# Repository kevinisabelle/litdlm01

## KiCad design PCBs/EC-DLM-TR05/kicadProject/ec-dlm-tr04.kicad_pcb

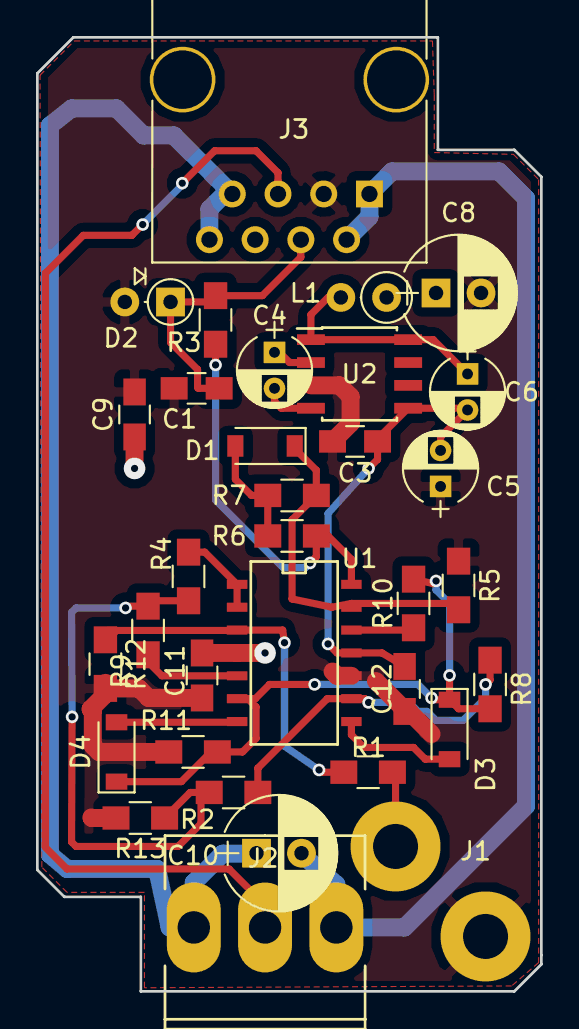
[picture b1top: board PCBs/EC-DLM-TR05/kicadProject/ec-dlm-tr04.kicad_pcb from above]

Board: 2 copper layers, 28.0 x 53.0 mm, 33 parts (0 on the bottom side), 23 nets.

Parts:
C1, C3, C9, C11, C12: 100n; C_0805_HandSoldering
C4, C5: 10u; CP_Radial_D4.0mm_P2.00mm
C6: 100u; CP_Radial_D4.0mm_P2.00mm
C8: 10u; CP_Radial_D6.3mm_P2.50mm
C10: 10uf; CP_Radial_D6.3mm_P2.50mm
D1: 1N4148; D_SOD-123
D2: 1N4148; D_DO-35_SOD27_P2.54mm_Vertical_AnodeUp
D3, D4: D; D_SOD-123
J1: input; WireConnection_2.50mmDrill
J2: LED Connector; Socket_MOLEX-KK-RM3-96mm_Lock_3pin_straight
J3: RJ45; RJ45_8
L1: Ferrite_Bead; L_Axial_L6.6mm_D2.7mm_P2.54mm_Vertical_Vishay_IM-2
R1, R7: 100k; R_0805_HandSoldering
R2, R3, R4, R5, R6, R8, R9, R10, R11: 10k; R_0805_HandSoldering
R12, R13: 1M; R_0805_HandSoldering
U1: TL074; SOIC-14_N
U2: TC1044S; SOIC-8_3.9x4.9mm_Pitch1.27mm

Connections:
ADCTrig: C1.2, D2.1, J3.4, R3.2
AGND: C1.1, C3.2, C5.1, C8.2, C9.1, C11.2, C12.2, D2.2, J1.1, J3.3, R5.2, R11.1, R12.2, R13.2, U1.10, U2.3
AVCC: C8.1, C9.2, C11.1, J3.6, L1.1, U1.4
AVSS: C3.1, C5.2, C6.2, C12.1, U1.11, U2.5
GND: C10.2, J2.1, J3.1, J3.2
L_OUT_5: J2.2, J3.5
unnamed: C4.1, U2.2
unnamed: C4.2, U2.4
unnamed: C6.1, L1.2, U2.1, U2.8
unnamed: D1.1, R5.1, R7.2, U1.13
unnamed: D1.2, R6.1, R7.1
unnamed: D3.1, D4.1, R8.1, R10.2, R11.2, U1.6
unnamed: D3.2, U1.8
unnamed: D4.2, U1.7
unnamed: J1.2, R1.2
unnamed: R1.1, R12.1, U1.3
unnamed: R2.1, R8.2, U1.9
unnamed: R3.1, R6.2, U1.14
unnamed: R4.2, U1.1, U1.2
unnamed: R9.2, U1.5
unnamed: R10.1, U1.12
unnamed: R2.2, R4.1, R9.1, R13.1
VCC5: C10.1, J2.3, J3.7, J3.8

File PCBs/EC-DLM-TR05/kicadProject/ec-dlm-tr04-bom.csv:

Reference, Value, Footprint, Datasheet
"J3","RJ45","Connectors:RJ45_8",""
"J2","LED Connector","Sockets_MOLEX_KK-System:Socket_MOLEX-KK-RM3-96mm_Lock_3pin_straight",""
"U1","TL074","SMD_Packages:SOIC-14_N",""
"R1","100k","Resistors_SMD:R_0805_HandSoldering",""
"J1","input","Wire_Connections_Bridges:WireConnection_2.50mmDrill",""
"R2","10k","Resistors_SMD:R_0805_HandSoldering",""
"R4","10k","Resistors_SMD:R_0805_HandSoldering",""
"R5","10k","Resistors_SMD:R_0805_HandSoldering",""
"R6","10k","Resistors_SMD:R_0805_HandSoldering",""
"D1","1N4148","Diodes_SMD:D_SOD-123",""
"D2","1N4148","Diodes_THT:D_DO-35_SOD27_P2.54mm_Vertical_AnodeUp",""
"R3","10k","Resistors_SMD:R_0805_HandSoldering",""
"C1","100n","Capacitors_SMD:C_0805_HandSoldering",""
"U2","TC1044S","Housings_SOIC:SOIC-8_3.9x4.9mm_Pitch1.27mm",""
"C4","10u","Capacitors_THT:CP_Radial_D4.0mm_P2.00mm",""
"C5","10u","Capacitors_THT:CP_Radial_D4.0mm_P2.00mm",""
"C6","100u","Capacitors_THT:CP_Radial_D4.0mm_P2.00mm",""
"L1","Ferrite_Bead","Inductors_THT:L_Axial_L6.6mm_D2.7mm_P2.54mm_Vertical_Vishay_IM-2",""
"R13","1M","Resistors_SMD:R_0805_HandSoldering",""
"R8","10k","Resistors_SMD:R_0805_HandSoldering",""
"D4","D","Diodes_SMD:D_SOD-123",""
"D3","D","Diodes_SMD:D_SOD-123",""
"R9","10k","Resistors_SMD:R_0805_HandSoldering",""
"R10","10k","Resistors_SMD:R_0805_HandSoldering",""
"R11","10k","Resistors_SMD:R_0805_HandSoldering",""
"R12","1M","Resistors_SMD:R_0805_HandSoldering",""
"R7","100k","Resistors_SMD:R_0805_HandSoldering",""
"C9","100n","Capacitors_SMD:C_0805_HandSoldering",""
"C10","10uf","Capacitors_THT:CP_Radial_D6.3mm_P2.50mm",""
"C3","100n","Capacitors_SMD:C_0805_HandSoldering",""
"C8","10u","Capacitors_THT:CP_Radial_D6.3mm_P2.50mm",""
"C11","100n","Capacitors_SMD:C_0805_HandSoldering",""
"C12","100n","Capacitors_SMD:C_0805_HandSoldering",""

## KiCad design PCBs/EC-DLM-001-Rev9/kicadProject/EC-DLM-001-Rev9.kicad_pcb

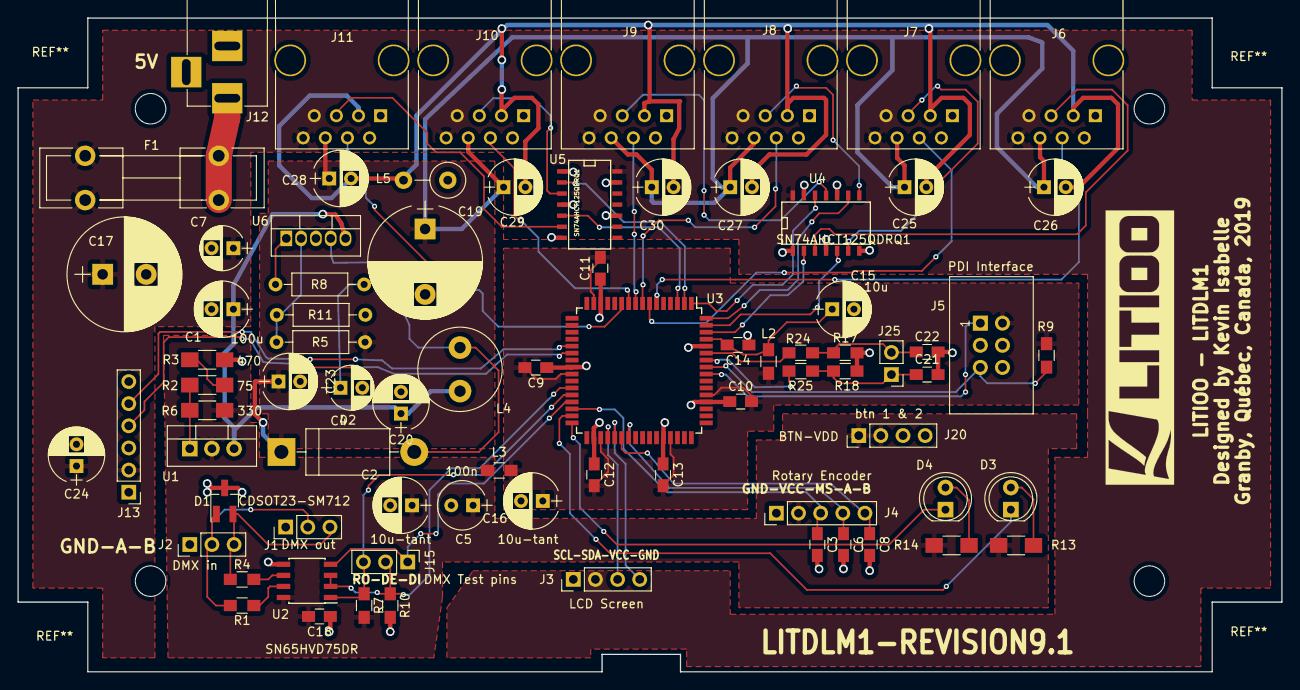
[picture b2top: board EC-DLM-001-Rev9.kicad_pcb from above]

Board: 2 copper layers, 145.0 x 75.0 mm, 78 parts (0 on the bottom side), 56 nets.

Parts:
C1: 100u; CP_Radial_D6.3mm_P2.50mm
C2, C16: 10u-tant; CP_Radial_D6.3mm_P2.50mm
C3, C6, C8, C9, C10, C11, C12, C13, C14, C18, C21, C22: 100n; C_0805_HandSoldering
C4: 0.33u; CP_Radial_D5.0mm_P2.50mm
C5: 100n; CP_Radial_Tantal_D5.5mm_P2.50mm
C7: 0.1u; CP_Radial_D5.0mm_P2.50mm
C15: 10u; CP_Radial_D6.3mm_P2.50mm
C17: 1000u; CP_Radial_D13.0mm_P5.00mm
C19: 680u; CP_Radial_D13.0mm_P7.50mm
C20, C23, C24, C25, C26, C27, C28, C29, C30: 100n; CP_Radial_D6.3mm_P2.50mm
D1: CDSOT23-SM712; SOT-23_Handsoldering
D2: 1N5821; D_DO-201AD_P15.24mm_Horizontal
D3, D4: LED; LED_D5.0mm
F1: Fuse; Fuseholder5x20_horiz_open_lateral_Type-II
J1: DMX out; Pin_Header_Straight_1x03_Pitch2.54mm
J2: DMX in; Pin_Header_Straight_1x03_Pitch2.54mm
J3: LCD Screen; Pin_Header_Straight_1x04_Pitch2.54mm
J4: Rotary Encoder; Pin_Header_Straight_1x05_Pitch2.54mm
J5: PDI Interface; IDC_Header_Straight_6pins
J6, J7, J8, J9, J10, J11: RJ45; RJ45_8
J12: BARREL_JACK
J13: Bluetooth Module; Pin_Header_Straight_1x06_Pitch2.54mm
J15: DMX Test pins; Pin_Header_Straight_1x03_Pitch2.54mm
J20: BTN-VDD; Pin_Header_Straight_1x04_Pitch2.54mm
J25: btn 1 & 2; Pin_Header_Straight_1x02_Pitch2.54mm
L2: Fer Bead; L_0805_HandSoldering
L3: 10uH; L_0805_HandSoldering
L4: 100uH; L_Radial_D9.5mm_P5.00mm_Fastron_07HVP
L5: 10uH; L_Axial_L9.5mm_D4.0mm_P5.08mm_Vertical_Fastron_SMCC
R1, R4: 10; R_0805_HandSoldering
R2: 75; R_1206_HandSoldering
R3: 470; R_1206_HandSoldering
R5: 17.3k; R_Axial_DIN0207_L6.3mm_D2.5mm_P10.16mm_Horizontal
R6: 330; R_1206_HandSoldering
R7, R10, R17, R18: 10k; R_0805_HandSoldering
R8: 2.2k; R_Axial_DIN0207_L6.3mm_D2.5mm_P10.16mm_Horizontal
R9: 10K; R_0805_HandSoldering
R11: 2k; R_Axial_DIN0207_L6.3mm_D2.5mm_P10.16mm_Horizontal
R13, R14: R; R_1206_HandSoldering
R24, R25: 220; R_0805_HandSoldering
U1: LM317T; TO-220-3_Vertical
U2: SN65HVD75DR; SOIC-8_3.9x4.9mm_Pitch1.27mm
U3: ATXMEGA64A3U-AU; TQFP-64_14x14mm_Pitch0.8mm
U4, U5: SN74AHCT125QDRQ1; SOIC-14_N
U6: LM2577; TO-220-5_Vertical

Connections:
+5V: F1.2, J12.1
/MAX485-A: R1.1, U2.7
/MAX485-B: R4.2, U2.6
ADCTrig1: J6.4, U3.6
ADCTrig2: J7.4, U3.7
ADCTrig3: J8.4, U3.8
ADCTrig4: J9.4, U3.9
ADCTrig5: J10.4, U3.10
ADCTrig6: J11.4, U3.11
AVCC: C19.1, C23.1, C25.1, C26.1, C27.1, C28.1, C29.1, C30.1, D2.1, J6.6, J7.6, J8.6, J9.6, J10.6, J11.6, R5.2
AnalogGND: C25.2, C26.2, C27.2, C28.2, C29.2, C30.2, J6.3, J7.3, J8.3, J9.3, J10.3, J11.3, L5.2
BTN1: R25.2, U3.58
BTN2: R24.2, U3.59
BT_RX: J13.5, U3.21
BT_TX: J13.4, U3.22
DE-RE: J15.2, R10.1, U2.2, U2.3, U3.27
DI: J15.1, U2.4, U3.29
ENCODER_A: C8.1, J4.5, U3.38
ENCODER_B: C6.1, J4.4, U3.39
ENCODER_MS: C3.1, J4.3, U3.30
GND: C1.2, C2.2, C3.2, C4.2, C5.2, C6.2, C7.2, C8.2, C9.1, C10.1, C11.1, C12.1, C13.1, C14.1, C15.2, C16.2, C17.2, C18.1, C19.2, C20.2, C21.2, C22.2, C23.2, C24.2, D1.3, J1.1, J2.1, J3.1, J4.1, J5.6, J6.1, J6.2, J7.1, J7.2, J8.1, J8.2, J9.1, J9.2, J10.1, J10.2, J11.1, J11.2, J12.2, J12.3, J13.3, L5.1, R3.1, R10.2, R11.2, R17.2, R18.2, U2.5, U3.14, U3.24, U3.34, U3.44, U3.52, U3.60, U4.1, U4.4, U4.7, U4.10, U4.13, U5.1, U5.4, U5.7, U5.10, U5.13, U6.3
L1_OUT_3.3: U3.62, U4.2
L1_OUT_5: J6.5, U4.3
L2_OUT_3.3: U3.63, U4.5
L2_OUT_5: J7.5, U4.6
L3_OUT_3.3: U3.64, U4.9
L3_OUT_5: J8.5, U4.8
L4_OUT_3.3: U3.1, U4.12
L4_OUT_5: J9.5, U4.11
L5_OUT_3.3: U3.2, U5.2
L5_OUT_5: J10.5, U5.3
L6_OUT_3.3: U3.3, U5.5
L6_OUT_5: J11.5, U5.6
LCD_SCL: J3.4, U3.37
LCD_SDA: J3.3, U3.36
LED1: D3.1, U3.31
LED2: D4.1, U3.32
unnamed: C4.1, R8.2
unnamed: C14.2, C15.1, L2.2, U3.61
unnamed: C21.1, J25.1, R18.1, R25.1
unnamed: C22.1, J25.2, R17.1, R24.1
unnamed: D1.1, J1.2, J2.2, R1.2
unnamed: D1.2, J1.3, J2.3, R4.1
unnamed: D2.2, L4.1, U6.4
unnamed: D3.2, R13.1
unnamed: D4.2, R14.1
unnamed: R2.1, R6.2, U1.1
unnamed: R2.2, R3.2
unnamed: R8.1, U6.1
unnamed: R5.1, R11.1, U6.2
PDI_CLK: J5.5, R9.1, U3.57
PDI_DATA: J5.1, U3.56
RO: J15.3, R7.1, U2.1, U3.28
VCC: C1.1, C7.1, C17.1, C20.1, C24.1, F1.1, J3.2, J6.7, J6.8, J7.7, J7.8, J8.7, J8.8, J9.7, J9.8, J10.7, J10.8, J11.7, J11.8, J13.2, L4.2, U1.3, U4.14, U5.14, U6.5
VDD: C2.1, C5.1, C18.2, J4.2, J20.1, J20.2, L3.1, R6.1, R7.2, R13.2, R14.2, U1.2, U2.8
VDD-Filtered: C9.2, C10.2, C11.2, C12.2, C13.2, C16.1, J5.2, L2.1, L3.2, R9.2, U3.15, U3.25, U3.35, U3.45, U3.53

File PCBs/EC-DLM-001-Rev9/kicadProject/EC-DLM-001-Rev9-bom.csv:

Reference, Value, Footprint, Datasheet
"U3","ATXMEGA64A3U-AU","Housings_QFP:TQFP-64_14x14mm_Pitch0.8mm",""
"C9","100n","Capacitors_SMD:C_0805_HandSoldering",""
"C10","100n","Capacitors_SMD:C_0805_HandSoldering",""
"C11","100n","Capacitors_SMD:C_0805_HandSoldering",""
"C12","100n","Capacitors_SMD:C_0805_HandSoldering",""
"C13","100n","Capacitors_SMD:C_0805_HandSoldering",""
"C14","100n","Capacitors_SMD:C_0805_HandSoldering",""
"J9","RJ45","Connectors:RJ45_8",""
"J11","RJ45","Connectors:RJ45_8",""
"J8","RJ45","Connectors:RJ45_8",""
"J10","RJ45","Connectors:RJ45_8",""
"L2","Fer Bead","Inductors_SMD:L_0805_HandSoldering",""
"U2","SN65HVD75DR","Housings_SOIC:SOIC-8_3.9x4.9mm_Pitch1.27mm",""
"U1","LM317T","TO_SOT_Packages_THT:TO-220-3_Vertical",""
"C1","100u","Capacitors_THT:CP_Radial_D6.3mm_P2.50mm",""
"C2","10u-tant","Capacitors_THT:CP_Radial_D6.3mm_P2.50mm",""
"C5","100n","Capacitors_THT:CP_Radial_Tantal_D5.5mm_P2.50mm",""
"R2","75","Resistors_SMD:R_1206_HandSoldering",""
"R3","470","Resistors_SMD:R_1206_HandSoldering",""
"R6","330","Resistors_SMD:R_1206_HandSoldering",""
"J5","PDI Interface","Connectors:IDC_Header_Straight_6pins",""
"L3","10uH","Inductors_SMD:L_0805_HandSoldering",""
"C16","10u-tant","Capacitors_THT:CP_Radial_D6.3mm_P2.50mm",""
"C15","10u","Capacitors_THT:CP_Radial_D6.3mm_P2.50mm",""
"R9","10K","Resistors_SMD:R_0805_HandSoldering",""
"R7","10k","Resistors_SMD:R_0805_HandSoldering",""
"R10","10k","Resistors_SMD:R_0805_HandSoldering",""
"J2","DMX in","Pin_Headers:Pin_Header_Straight_1x03_Pitch2.54mm",""
"J1","DMX out","Pin_Headers:Pin_Header_Straight_1x03_Pitch2.54mm",""
"J4","Rotary Encoder","Pin_Headers:Pin_Header_Straight_1x05_Pitch2.54mm",""
"J3","LCD Screen","Pin_Headers:Pin_Header_Straight_1x04_Pitch2.54mm",""
"C8","100n","Capacitors_SMD:C_0805_HandSoldering",""
"C6","100n","Capacitors_SMD:C_0805_HandSoldering",""
"C3","100n","Capacitors_SMD:C_0805_HandSoldering",""
"J12","BARREL_JACK","Connectors:BARREL_JACK",""
"J15","DMX Test pins","Pin_Headers:Pin_Header_Straight_1x03_Pitch2.54mm",""
"C17","1000u","Capacitors_THT:CP_Radial_D13.0mm_P5.00mm",""
"D4","LED","LEDs:LED_D5.0mm",""
"R14","R","Resistors_SMD:R_1206_HandSoldering",""
"R13","R","Resistors_SMD:R_1206_HandSoldering",""
"D3","LED","LEDs:LED_D5.0mm",""
"U4","SN74AHCT125QDRQ1","SMD_Packages:SOIC-14_N",""
"U5","SN74AHCT125QDRQ1","SMD_Packages:SOIC-14_N",""
"R1","10","Resistors_SMD:R_0805_HandSoldering",""
"R4","10","Resistors_SMD:R_0805_HandSoldering",""
"C18","100n","Capacitors_SMD:C_0805_HandSoldering",""
"D1","CDSOT23-SM712","TO_SOT_Packages_SMD:SOT-23_Handsoldering",""
"J25","btn 1 & 2","Pin_Headers:Pin_Header_Straight_1x02_Pitch2.54mm",""
"R24","220","Resistors_SMD:R_0805_HandSoldering",""
"R25","220","Resistors_SMD:R_0805_HandSoldering",""
"R17","10k","Resistors_SMD:R_0805_HandSoldering",""
"R18","10k","Resistors_SMD:R_0805_HandSoldering",""
"J20","BTN-VDD","Pin_Headers:Pin_Header_Straight_1x04_Pitch2.54mm",""
"C22","100n","Capacitors_SMD:C_0805_HandSoldering",""
"C21","100n","Capacitors_SMD:C_0805_HandSoldering",""
"J6","RJ45","Connectors:RJ45_8",""
"J7","RJ45","Connectors:RJ45_8",""
"F1","Fuse","Fuse_Holders_and_Fuses:Fuseholder5x20_horiz_open_lateral_Type-II",""
"L4","100uH","Inductors_THT:L_Radial_D9.5mm_P5.00mm_Fastron_07HVP",""
"J13","Bluetooth Module","Pin_Headers:Pin_Header_Straight_1x06_Pitch2.54mm",""
"L5","10uH","Inductors_THT:L_Axial_L9.5mm_D4.0mm_P5.08mm_Vertical_Fastron_SMCC",""
"D2","1N5821","Diodes_THT:D_DO-201AD_P15.24mm_Horizontal",""
"C4","0.33u","Capacitors_THT:CP_Radial_D5.0mm_P2.50mm",""
"R11","2k","Resistors_THT:R_Axial_DIN0207_L6.3mm_D2.5mm_P10.16mm_Horizontal",""
"C19","680u","Capacitors_THT:CP_Radial_D13.0mm_P7.50mm",""
"R8","2.2k","Resistors_THT:R_Axial_DIN0207_L6.3mm_D2.5mm_P10.16mm_Horizontal",""
"R5","17.3k","Resistors_THT:R_Axial_DIN0207_L6.3mm_D2.5mm_P10.16mm_Horizontal",""
"C7","0.1u","Capacitors_THT:CP_Radial_D5.0mm_P2.50mm",""
"C20","100n","Capacitors_THT:CP_Radial_D6.3mm_P2.50mm",""
"C23","100n","Capacitors_THT:CP_Radial_D6.3mm_P2.50mm",""
"U6","LM2577","TO_SOT_Packages_THT:TO-220-5_Vertical",""
"C25","100n","Capacitors_THT:CP_Radial_D6.3mm_P2.50mm",""
"C26","100n","Capacitors_THT:CP_Radial_D6.3mm_P2.50mm",""
"C28","100n","Capacitors_THT:CP_Radial_D6.3mm_P2.50mm",""
"C29","100n","Capacitors_THT:CP_Radial_D6.3mm_P2.50mm",""
"C27","100n","Capacitors_THT:CP_Radial_D6.3mm_P2.50mm",""
"C30","100n","Capacitors_THT:CP_Radial_D6.3mm_P2.50mm",""
"C24","100n","Capacitors_THT:CP_Radial_D6.3mm_P2.50mm",""

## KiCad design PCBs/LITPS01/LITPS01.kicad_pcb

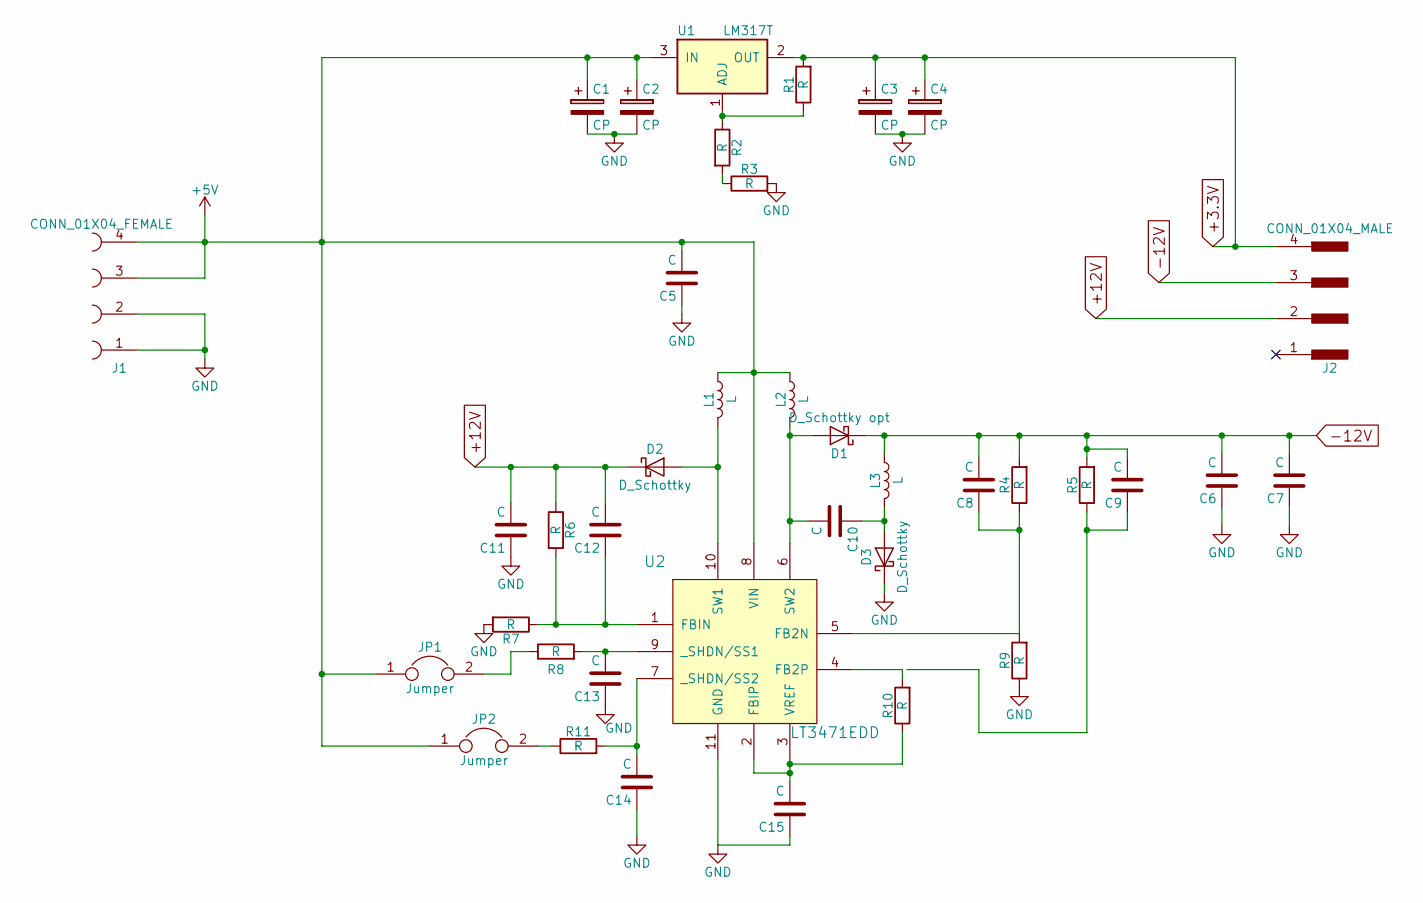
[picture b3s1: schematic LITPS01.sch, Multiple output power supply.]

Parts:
C1: CP; CP_Radial_D10.0mm_P5.00mm
C2, C3, C4: CP; CP_Radial_D5.0mm_P2.50mm
C5, C6, C7, C8, C9, C10, C11, C12, C13, C14, C15: C; C_1206_HandSoldering
D1: D_Schottky opt; D_PowerDI-123
D2, D3: D_Schottky; D_PowerDI-123
J1: CONN_01X04_FEMALE; Pin_Header_Straight_1x04_Pitch2.54mm
J2: CONN_01X04_MALE; Pin_Header_Straight_1x04_Pitch2.54mm
JP1, JP2: Jumper; Pin_Header_Straight_1x02_Pitch2.54mm
L1, L2, L3: L; Inductor_Taiyo-Yuden_NR-40xx_HandSoldering
R1, R2, R3, R4, R5, R6, R7, R8, R9, R10, R11: R; R_1206_HandSoldering
U1: LM317T; TO-220_Vertical
U2: LT3471EDD; DFN-10-1EP_3x3mm_Pitch0.5mm

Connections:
+3.3V: C3.1, C4.1, J2.4, R1.2, U1.2 (OUT)
+5V: C1.1, C2.1, C5.2, J1.3, J1.4, JP1.1, JP2.1, L1.1, L2.1, U1.3 (IN), U2.8 (VIN)
+12V: C11.2, C12.2, D2.1 (K), J2.2, R6.1
-12V: C6.2, C7.2, C8.2, C9.2, D1.1 (K), J2.3, L3.1, R4.2, R5.2
GND: C1.2, C2.2, C3.2, C4.2, C5.1, C6.1, C7.1, C11.1, C13.1, C14.1, C15.1, D3.1 (K), J1.1, J1.2, R3.2, R7.2, R9.1, U2.11 (GND)
unnamed: C8.1, R4.1, R9.2, U2.5 (FB2N)
unnamed: C9.1, R5.1
unnamed: C10.1, D3.2 (A), L3.2
unnamed: C10.2, D1.2 (A), L2.2, U2.6 (SW2)
unnamed: C12.1, R6.2, R7.1, U2.1 (FBIN)
unnamed: C13.2, R8.2, U2.9 (_SHDN/SS1)
unnamed: C14.2, R11.2, U2.7 (_SHDN/SS2)
unnamed: C15.2, R10.1, U2.2 (FBIP), U2.3 (VREF)
unnamed: D2.2 (A), L1.2, U2.10 (SW1)
unnamed: JP1.2, R8.1
unnamed: JP2.2, R11.1
unnamed: R1.1, R2.1, U1.1 (ADJ)
unnamed: R2.2, R3.1
unnamed: R10.2, U2.4 (FB2P)

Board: 2 copper layers, 37 parts (0 on the bottom side), 19 nets, no tracks yet.

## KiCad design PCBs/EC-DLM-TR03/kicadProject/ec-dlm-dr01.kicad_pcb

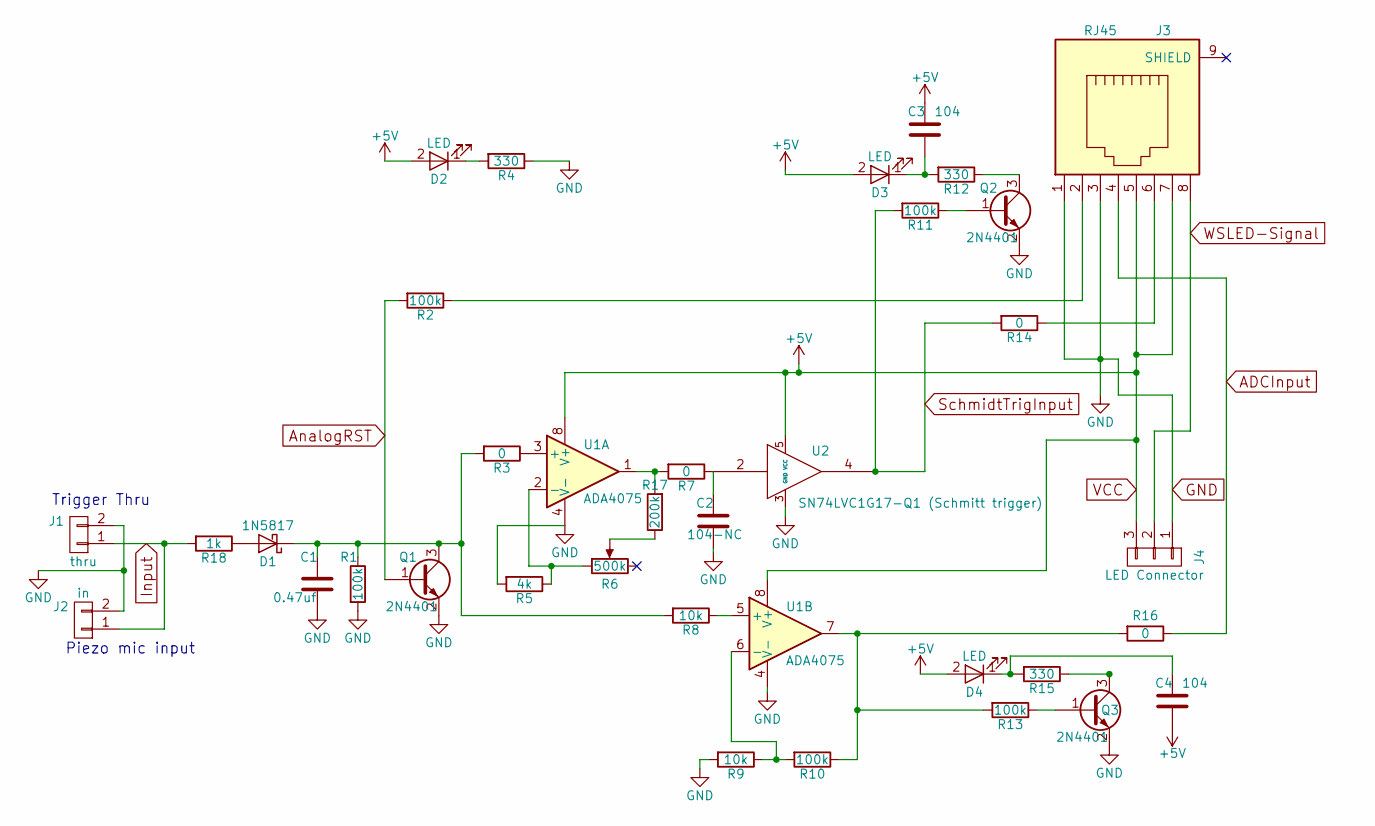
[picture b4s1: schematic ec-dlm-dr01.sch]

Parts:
C1: 0.47uf; C_1206_HandSoldering
C2: 104-NC; C_0805_HandSoldering
C3, C4: 104; C_0805_HandSoldering
D1: 1N5817; D_SOD-323_HandSoldering
D2, D3, D4: LED; LED_0805_HandSoldering
J1: thru; WireConnection_2.50mmDrill
J2: in; WireConnection_2.50mmDrill
J3: RJ45; RJ45_8
J4: LED Connector; Socket_MOLEX-KK-RM3-96mm_Lock_3pin_straight
Q1, Q2, Q3: 2N4401; SOT-23_Handsoldering
R1, R2, R10, R11, R13: 100k; R_0805_HandSoldering
R3, R7, R14, R16: 0; R_0805_HandSoldering
R4, R12, R15: 330; R_0805_HandSoldering
R5: 4k; R_0805_HandSoldering
R6: 500k; TrimPot_Straight_2x03_Pitch2.54mm
R8, R9: 10k; R_0805_HandSoldering
R17: 200k; R_0805_HandSoldering
R18: 1k; R_0805_HandSoldering
U1: ADA4075; SOIC-8_3.9x4.9mm_Pitch1.27mm
U2: SN74LVC1G17-Q1 (Schmitt trigger); SOT-353_SC-70-5_Handsoldering

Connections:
ADCInput: J3.4, R16.1
AnalogRST: Q1.1 (B), R2.2
GND: C1.2, C2.2, J1.2, J2.2, J3.1, J3.3, J4.1, Q1.2 (E), Q2.2 (E), Q3.2 (E), R1.2, R4.1, R5.2, R9.2, U1.4 (V-), U2.3 (GND)
Input: J1.1, J2.1, R18.2
unnamed: C1.1, D1.1 (K), Q1.3 (C), R1.1, R3.2, R8.2
unnamed: C2.1, R7.1, U2.2
unnamed: C3.2, D3.1 (K), R12.2
unnamed: C4.1, D4.1 (K), R15.2
unnamed: D1.2 (A), R18.1
unnamed: D2.1 (K), R4.2
unnamed: J3.2, R2.1
unnamed: J3.6, R14.1
unnamed: Q2.1 (B), R11.1
unnamed: Q2.3 (C), R12.1
unnamed: Q3.1 (B), R13.1
unnamed: Q3.3 (C), R15.1
unnamed: R3.1, U1.3 (+)
unnamed: R5.1, R6.1, U1.2 (-)
unnamed: R8.1, U1.5 (+)
unnamed: R10.1, R13.2, R16.2, U1.7
unnamed: R9.1, R10.2, U1.6 (-)
unnamed: R6.2, R17.1
unnamed: R7.2, R17.2, U1.1
SchmidtTrigInput: R11.2, R14.2, U2.4
VCC: C3.1, C4.2, D2.2 (A), D3.2 (A), D4.2 (A), J3.5, J3.7, J4.3, U1.8 (V+), U2.5 (VCC)
WSLED-Signal: J3.8, J4.2

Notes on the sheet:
Piezo mic input
Trigger Thru

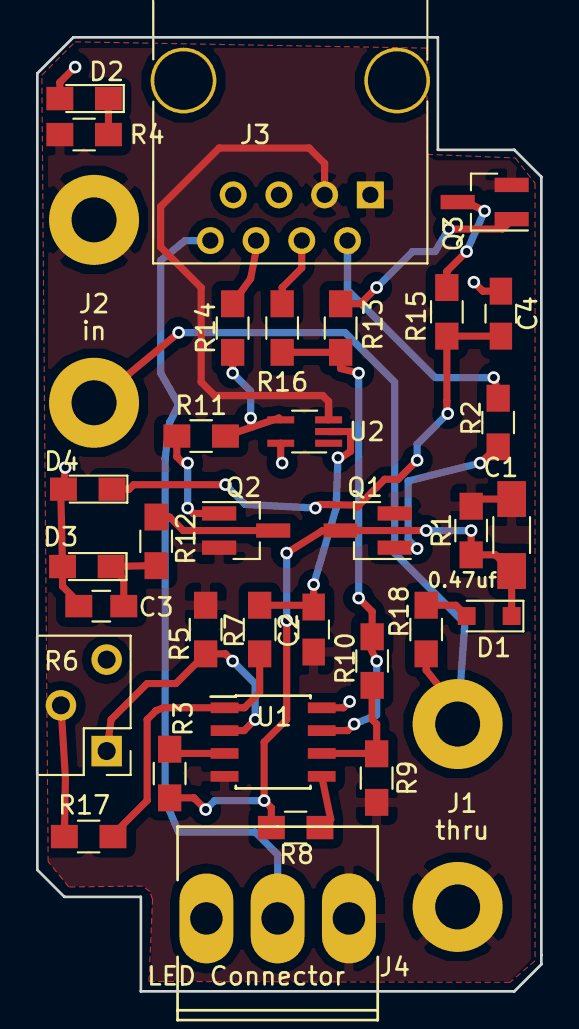
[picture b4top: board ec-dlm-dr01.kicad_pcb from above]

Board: 2 copper layers, 28.0 x 53.0 mm, 35 parts (0 on the bottom side), 26 nets.

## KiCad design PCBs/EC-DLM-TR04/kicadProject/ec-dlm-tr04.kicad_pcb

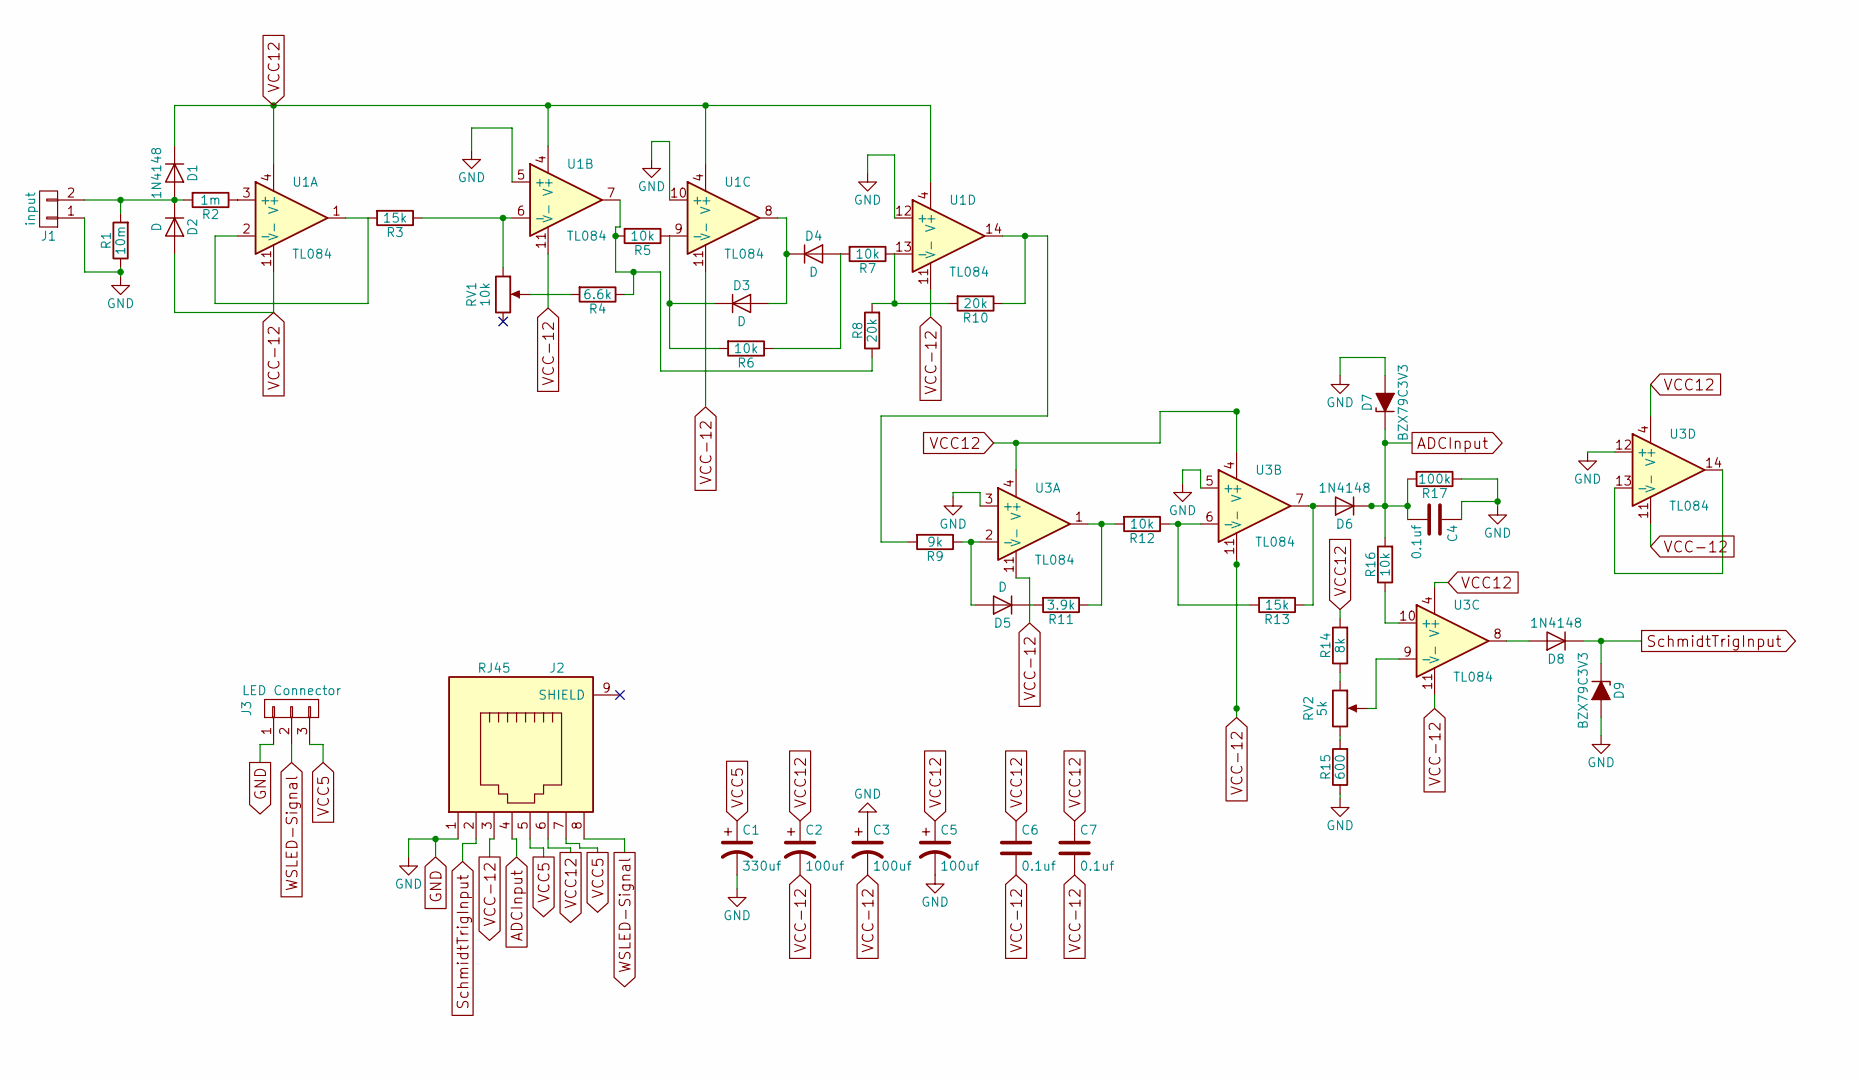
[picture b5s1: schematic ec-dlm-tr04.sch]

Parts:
C1: 330uf; CP_Radial_D5.0mm_P2.00mm
C2, C3, C5: 100uf; CP_Radial_D4.0mm_P1.50mm
C4, C6, C7: 0.1uf; C_0805_HandSoldering
D1, D6, D8: 1N4148; D_SOD-123
D2, D3, D4, D5: D; D_SOD-123
D7, D9: BZX79C3V3; D_DO-35_SOD27_P2.54mm_Vertical_AnodeUp
J1: input; WireConnection_2.50mmDrill
J2: RJ45; RJ45_8
J3: LED Connector; Socket_MOLEX-KK-RM3-96mm_Lock_3pin_straight
R1: 10m; R_0805_HandSoldering
R2: 1m; R_0805_HandSoldering
R3, R13: 15k; R_0805_HandSoldering
R4: 6.6k; R_0805_HandSoldering
R5, R6, R7, R12, R16: 10k; R_0805_HandSoldering
R8, R10: 20k; R_0805_HandSoldering
R9: 9k; R_0805_HandSoldering
R11: 3.9k; R_0805_HandSoldering
R14: 8k; R_0805_HandSoldering
R15: 600; R_0805_HandSoldering
R17: 100k; R_0805_HandSoldering
RV1: 10k; Potentiometer_WirePads_Small
RV2: 5k; Potentiometer_WirePads_Small
U1, U3: TL084; SOIC-14_N

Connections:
ADCInput: C4.2, D6.1 (K), D7.1 (K), J2.4, R16.2, R17.2
GND: C1.2, C3.1, C4.1, C5.2, D7.2 (A), D9.2 (A), J1.1, J2.1, J3.1, R1.1, R15.1, R17.1, U1.5 (+), U1.10 (+), U1.12 (+), U3.3 (+), U3.5 (+), U3.12 (+)
unnamed: D1.2 (A), D2.1 (K), J1.2, R1.2, R2.2
unnamed: D3.1 (K), R5.1, R6.2, U1.9 (-)
unnamed: D3.2 (A), D4.1 (K), U1.8
unnamed: D4.2 (A), R6.1, R7.2
unnamed: D5.1 (K), R11.2
unnamed: D5.2 (A), R9.1, U3.2 (-)
unnamed: D6.2 (A), R13.1, U3.7
unnamed: D8.2 (A), U3.8
unnamed: R2.1, U1.3 (+)
unnamed: R3.1, RV1.1, U1.6 (-)
unnamed: R3.2, U1.1, U1.2 (-)
unnamed: R4.1, R5.2, R8.1, U1.7
unnamed: R4.2, RV1.2
unnamed: R9.2, R10.1, U1.14
unnamed: R7.1, R8.2, R10.2, U1.13 (-)
unnamed: R11.1, R12.2, U3.1
unnamed: R12.1, R13.2, U3.6 (-)
unnamed: R14.1, RV2.1
unnamed: R15.2, RV2.3
unnamed: R16.1, U3.10 (+)
unnamed: RV2.2, U3.9 (-)
unnamed: U3.13 (-), U3.14
SchmidtTrigInput: D8.1 (K), D9.1 (K), J2.2
VCC5: C1.1, J2.5, J2.7, J3.3
VCC12: C2.1, C5.1, C6.1, C7.1, D1.1 (K), J2.6, R14.2, U1.4 (V+), U3.4 (V+)
VCC-12: C2.2, C3.2, C6.2, C7.2, D2.2 (A), J2.3, U1.11 (V-), U3.11 (V-)
WSLED-Signal: J2.8, J3.2

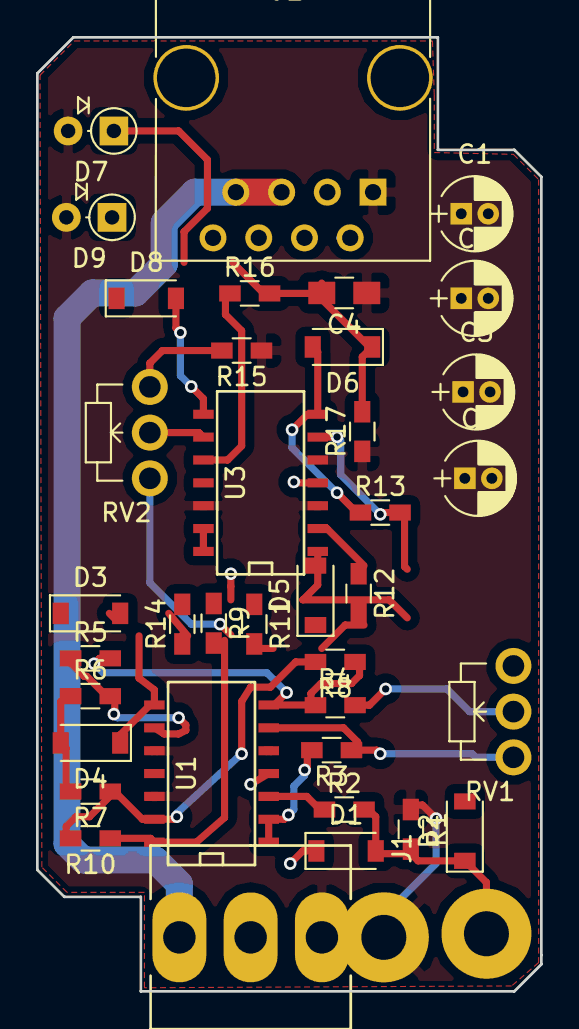
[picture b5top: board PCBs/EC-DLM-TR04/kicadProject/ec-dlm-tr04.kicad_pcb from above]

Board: 2 copper layers, 28.0 x 53.0 mm, 38 parts (0 on the bottom side), 29 nets.

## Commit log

2019-02-07 no message
2019-02-09 Working without analog trigger.
2019-02-09 Ajout d'animation.
2019-02-17 Working on DLM pcb rev9
2019-02-18 TR04 + DLM01 REV9 adjustments.
2019-02-28 New Main board.
2019-03-03 Revision board rev9
2019-03-05 New board pour production
2019-03-28 PCB Rouge
2019-08-29 Revision TR05 (Board rouge satellite) selon les tests.
2019-11-03 Memoire 192U et tests pour plantage du LDC
2019-11-28 Fixed screen corruption problem.
2019-12-01 Add create anim program
2019-12-11 Fix pour les lumières internes ainsi que le bouton qui ne réagissait pas bien
2023-01-07 Updates for ADC
2024-09-17 midi support
2024-09-30 Menu updates for midi
